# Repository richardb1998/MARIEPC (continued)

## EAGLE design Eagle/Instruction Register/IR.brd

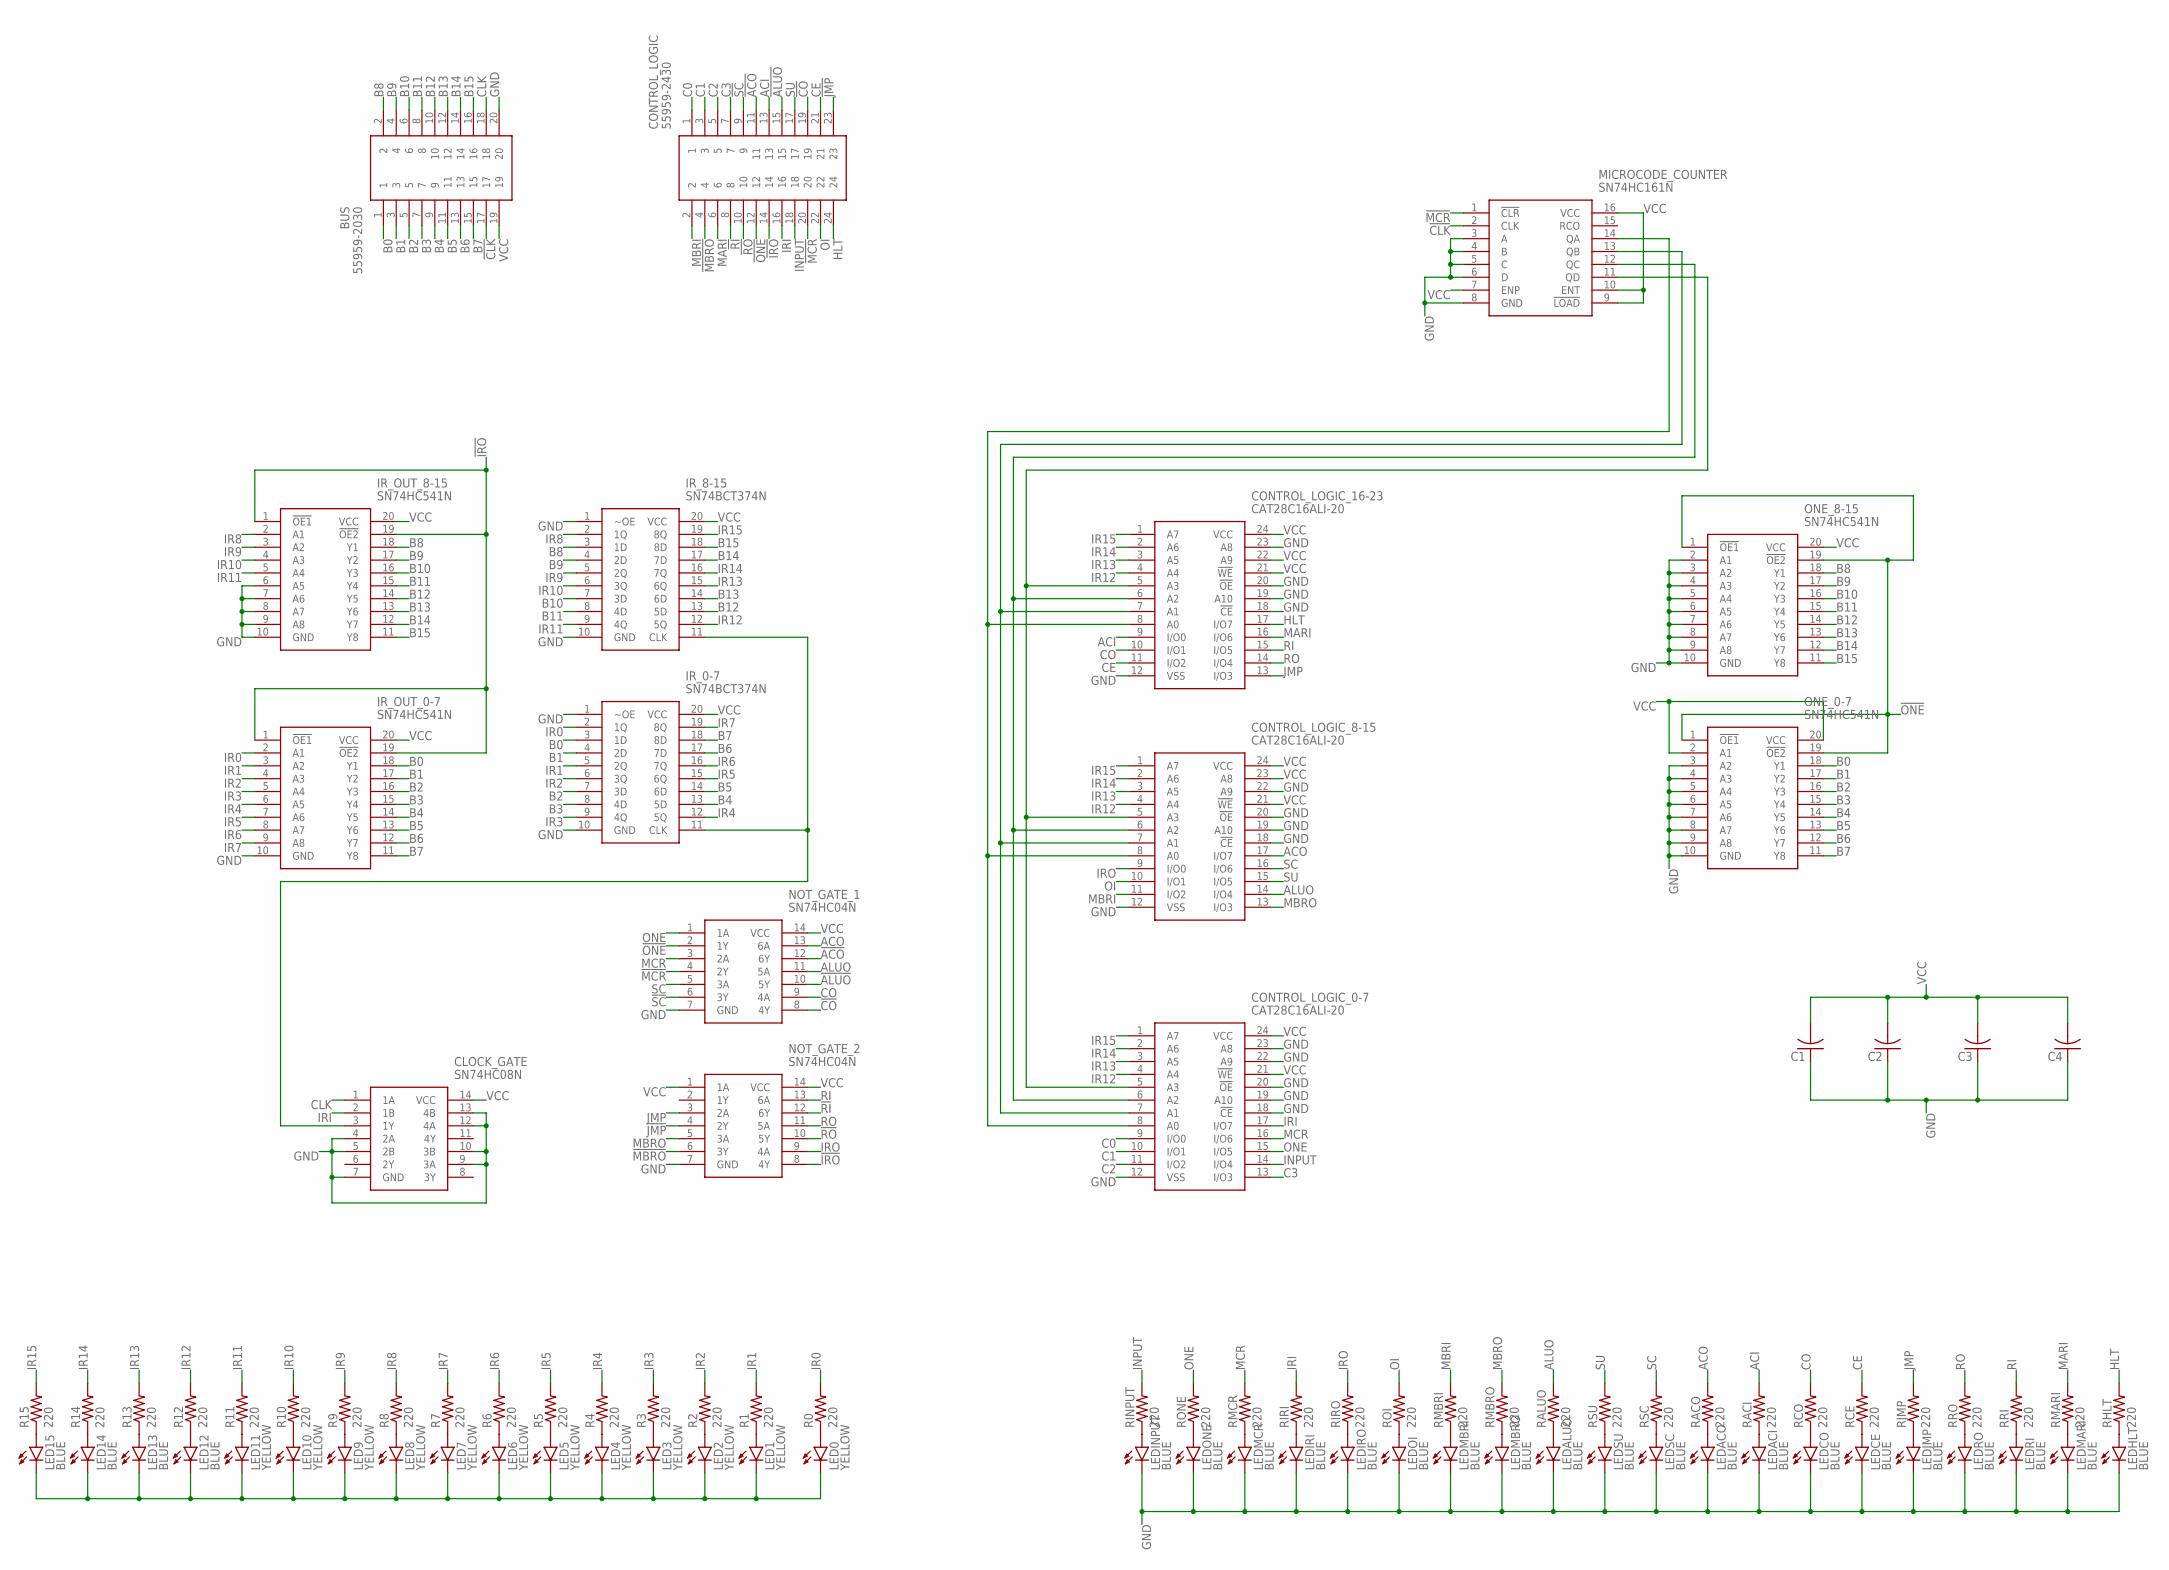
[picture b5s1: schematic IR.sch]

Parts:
BUS: 55959-2030; 55959-2030_1
C1, C2, C3, C4: C-US025-024X044; C025-024X044
CLOCK_GATE: SN74HC08N; DIP794W53P254L1930H508Q14N
CONTROL_LOGIC: 55959-2430; 559592430
CONTROL_LOGIC_0-7, CONTROL_LOGIC_8-15, CONTROL_LOGIC_16-23: CAT28C16ALI-20; DIP1651W55P254L3188H635Q24N
IR_0-7, IR_8-15: SN74BCT374N; DIP254P762X508-20
IR_OUT_0-7, IR_OUT_8-15: SN74HC541N; DIP794W53P254L2540H508Q20N
LED0, LED1, LED2, LED3, LED4, LED5, LED6, LED7, LED8, LED9, LED10, LED11: YELLOW; LED3MM
LED12, LED13, LED14, LED15: BLUE; LED3MM
LEDACI: BLUE; LED3MM
LEDACO: BLUE; LED3MM
LEDALUO: BLUE; LED3MM
LEDCE: BLUE; LED3MM
LEDCO: BLUE; LED3MM
LEDHLT: BLUE; LED3MM
LEDINPUT: BLUE; LED3MM
LEDIRI: BLUE; LED3MM
LEDIRO: BLUE; LED3MM
LEDJMP: BLUE; LED3MM
LEDMARI: BLUE; LED3MM
LEDMBRI: BLUE; LED3MM
LEDMBRO: BLUE; LED3MM
LEDMCR: BLUE; LED3MM
LEDOI: BLUE; LED3MM
LEDONE: BLUE; LED3MM
LEDRI: BLUE; LED3MM
LEDRO: BLUE; LED3MM
LEDSC: BLUE; LED3MM
LEDSU: BLUE; LED3MM
MICROCODE_COUNTER: SN74HC161N; DIP794W53P254L1930H508Q16N
NOT_GATE_1, NOT_GATE_2: SN74HC04N; DIP794W53P254L1930H508Q14N
ONE_0-7, ONE_8-15: SN74HC541N; DIP794W53P254L2540H508Q20N
R0, R1, R2, R3, R4, R5, R6, R7, R8, R9, R10, R11, R12, R13, R14, R15: 220; 0204/7
RACI: 220; 0204/7
RACO: 220; 0204/7
RALUO: 220; 0204/7
RCE: 220; 0204/7
RCO: 220; 0204/7
RHLT: 220; 0204/7
RINPUT: 220; 0204/7
RIRI: 220; 0204/7
RIRO: 220; 0204/7
RJMP: 220; 0204/7
RMARI: 220; 0204/7
RMBRI: 220; 0204/7
RMBRO: 220; 0204/7
RMCR: 220; 0204/7
ROI: 220; 0204/7
RONE: 220; 0204/7
RRI: 220; 0204/7
RRO: 220; 0204/7
RSC: 220; 0204/7
RSU: 220; 0204/7

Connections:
!ACO: CONTROL_LOGIC.11, NOT_GATE_1.12 (6Y)
!ALUO: CONTROL_LOGIC.15, NOT_GATE_1.10 (5Y)
!CLK: BUS.17, MICROCODE_COUNTER.2 (CLK)
!CO: CONTROL_LOGIC.19, NOT_GATE_1.8 (4Y)
!IRO: CONTROL_LOGIC.14, IR_OUT_0-7.1 (!OE1), IR_OUT_0-7.19 (!OE2), IR_OUT_8-15.1 (!OE1), IR_OUT_8-15.19 (!OE2), NOT_GATE_2.8 (4Y)
!JMP: CONTROL_LOGIC.23, NOT_GATE_2.4 (2Y)
!MBRO: CONTROL_LOGIC.4, NOT_GATE_2.6 (3Y)
!MCR: CONTROL_LOGIC.20, MICROCODE_COUNTER.1 (!CLR), NOT_GATE_1.4 (2Y)
!ONE: CONTROL_LOGIC.12, NOT_GATE_1.2 (1Y), ONE_0-7.1 (!OE1), ONE_0-7.19 (!OE2), ONE_8-15.1 (!OE1), ONE_8-15.19 (!OE2)
!RI: CONTROL_LOGIC.8, NOT_GATE_2.12 (6Y)
!RO: CONTROL_LOGIC.10, NOT_GATE_2.10 (5Y)
!SC: CONTROL_LOGIC.9, NOT_GATE_1.6 (3Y)
ACI: CONTROL_LOGIC.13, CONTROL_LOGIC_16-23.9 (I/O0), RACI.2
ACO: CONTROL_LOGIC_8-15.17 (I/O7), NOT_GATE_1.13 (6A), RACO.2
ALUO: CONTROL_LOGIC_8-15.14 (I/O4), NOT_GATE_1.11 (5A), RALUO.2
B0: BUS.1, IR_0-7.3 (1D), IR_OUT_0-7.18 (Y1), ONE_0-7.18 (Y1)
B1: BUS.3, IR_0-7.4 (2D), IR_OUT_0-7.17 (Y2), ONE_0-7.17 (Y2)
B2: BUS.5, IR_0-7.7 (3D), IR_OUT_0-7.16 (Y3), ONE_0-7.16 (Y3)
B3: BUS.7, IR_0-7.8 (4D), IR_OUT_0-7.15 (Y4), ONE_0-7.15 (Y4)
B4: BUS.9, IR_0-7.13 (5D), IR_OUT_0-7.14 (Y5), ONE_0-7.14 (Y5)
B5: BUS.11, IR_0-7.14 (6D), IR_OUT_0-7.13 (Y6), ONE_0-7.13 (Y6)
B6: BUS.13, IR_0-7.17 (7D), IR_OUT_0-7.12 (Y7), ONE_0-7.12 (Y7)
B7: BUS.15, IR_0-7.18 (8D), IR_OUT_0-7.11 (Y8), ONE_0-7.11 (Y8)
B8: BUS.2, IR_8-15.3 (1D), IR_OUT_8-15.18 (Y1), ONE_8-15.18 (Y1)
B9: BUS.4, IR_8-15.4 (2D), IR_OUT_8-15.17 (Y2), ONE_8-15.17 (Y2)
B10: BUS.6, IR_8-15.7 (3D), IR_OUT_8-15.16 (Y3), ONE_8-15.16 (Y3)
B11: BUS.8, IR_8-15.8 (4D), IR_OUT_8-15.15 (Y4), ONE_8-15.15 (Y4)
B12: BUS.10, IR_8-15.13 (5D), IR_OUT_8-15.14 (Y5), ONE_8-15.14 (Y5)
B13: BUS.12, IR_8-15.14 (6D), IR_OUT_8-15.13 (Y6), ONE_8-15.13 (Y6)
B14: BUS.14, IR_8-15.17 (7D), IR_OUT_8-15.12 (Y7), ONE_8-15.12 (Y7)
B15: BUS.16, IR_8-15.18 (8D), IR_OUT_8-15.11 (Y8), ONE_8-15.11 (Y8)
C0: CONTROL_LOGIC.1, CONTROL_LOGIC_0-7.9 (I/O0)
C1: CONTROL_LOGIC.3, CONTROL_LOGIC_0-7.10 (I/O1)
C2: CONTROL_LOGIC.5, CONTROL_LOGIC_0-7.11 (I/O2)
C3: CONTROL_LOGIC.7, CONTROL_LOGIC_0-7.13 (I/O3)
CE: CONTROL_LOGIC.21, CONTROL_LOGIC_16-23.11 (I/O2), RCE.2
CLK: BUS.18, CLOCK_GATE.1 (1A)
CO: CONTROL_LOGIC_16-23.10 (I/O1), NOT_GATE_1.9 (4A), RCO.2
GND: BUS.20, C1.1, C2.1, C3.1, C4.1, CLOCK_GATE.4 (2A), CLOCK_GATE.5 (2B), CLOCK_GATE.7 (GND), CLOCK_GATE.9 (3A), CLOCK_GATE.10 (3B), CLOCK_GATE.12 (4A), CLOCK_GATE.13 (4B), CONTROL_LOGIC_0-7.12 (VSS), CONTROL_LOGIC_0-7.18 (!CE), CONTROL_LOGIC_0-7.19 (A10), CONTROL_LOGIC_0-7.20 (!OE), CONTROL_LOGIC_0-7.22 (A9), CONTROL_LOGIC_0-7.23 (A8), CONTROL_LOGIC_8-15.12 (VSS), CONTROL_LOGIC_8-15.18 (!CE), CONTROL_LOGIC_8-15.19 (A10), CONTROL_LOGIC_8-15.20 (!OE), CONTROL_LOGIC_8-15.22 (A9), CONTROL_LOGIC_16-23.12 (VSS), CONTROL_LOGIC_16-23.18 (!CE), CONTROL_LOGIC_16-23.19 (A10), CONTROL_LOGIC_16-23.20 (!OE), CONTROL_LOGIC_16-23.23 (A8), IR_0-7.1 (~OE), IR_0-7.10 (GND), IR_8-15.1 (~OE), IR_8-15.10 (GND), IR_OUT_0-7.10 (GND), IR_OUT_8-15.6 (A5), IR_OUT_8-15.7 (A6), IR_OUT_8-15.8 (A7), IR_OUT_8-15.9 (A8), IR_OUT_8-15.10 (GND), LEDACI.K (C), LEDACO.K (C), LEDALUO.K (C), LEDCE.K (C), LEDCO.K (C), LEDHLT.K (C), LEDINPUT.K (C), LEDIRI.K (C), LEDIRO.K (C), LEDJMP.K (C), LEDMARI.K (C), LEDMBRI.K (C), LEDMBRO.K (C), LEDMCR.K (C), LEDOI.K (C), LEDONE.K (C), LEDRI.K (C), LEDRO.K (C), LEDSC.K (C), LEDSU.K (C), MICROCODE_COUNTER.3 (A), MICROCODE_COUNTER.4 (B), MICROCODE_COUNTER.5 (C), MICROCODE_COUNTER.6 (D), MICROCODE_COUNTER.8 (GND), NOT_GATE_1.7 (GND), NOT_GATE_2.7 (GND), ONE_0-7.3 (A2), ONE_0-7.4 (A3), ONE_0-7.5 (A4), ONE_0-7.6 (A5), ONE_0-7.7 (A6), ONE_0-7.8 (A7), ONE_0-7.9 (A8), ONE_0-7.10 (GND), ONE_8-15.2 (A1), ONE_8-15.3 (A2), ONE_8-15.4 (A3), ONE_8-15.5 (A4), ONE_8-15.6 (A5), ONE_8-15.7 (A6), ONE_8-15.8 (A7), ONE_8-15.9 (A8), ONE_8-15.10 (GND)
HLT: CONTROL_LOGIC.24, CONTROL_LOGIC_16-23.17 (I/O7), RHLT.2
INPUT: CONTROL_LOGIC.18, CONTROL_LOGIC_0-7.14 (I/O4), RINPUT.2
IR0: IR_0-7.2 (1Q), IR_OUT_0-7.2 (A1), R0.2
IR1: IR_0-7.5 (2Q), IR_OUT_0-7.3 (A2), R1.2
IR2: IR_0-7.6 (3Q), IR_OUT_0-7.4 (A3), R2.2
IR3: IR_0-7.9 (4Q), IR_OUT_0-7.5 (A4), R3.2
IR4: IR_0-7.12 (5Q), IR_OUT_0-7.6 (A5), R4.2
IR5: IR_0-7.15 (6Q), IR_OUT_0-7.7 (A6), R5.2
IR6: IR_0-7.16 (7Q), IR_OUT_0-7.8 (A7), R6.2
IR7: IR_0-7.19 (8Q), IR_OUT_0-7.9 (A8), R7.2
IR8: IR_8-15.2 (1Q), IR_OUT_8-15.2 (A1), R8.2
IR9: IR_8-15.5 (2Q), IR_OUT_8-15.3 (A2), R9.2
IR10: IR_8-15.6 (3Q), IR_OUT_8-15.4 (A3), R10.2
IR11: IR_8-15.9 (4Q), IR_OUT_8-15.5 (A4), R11.2
IR12: CONTROL_LOGIC_0-7.4 (A4), CONTROL_LOGIC_8-15.4 (A4), CONTROL_LOGIC_16-23.4 (A4), IR_8-15.12 (5Q), R12.2
IR13: CONTROL_LOGIC_0-7.3 (A5), CONTROL_LOGIC_8-15.3 (A5), CONTROL_LOGIC_16-23.3 (A5), IR_8-15.15 (6Q), R13.2
IR14: CONTROL_LOGIC_0-7.2 (A6), CONTROL_LOGIC_8-15.2 (A6), CONTROL_LOGIC_16-23.2 (A6), IR_8-15.16 (7Q), R14.2
IR15: CONTROL_LOGIC_0-7.1 (A7), CONTROL_LOGIC_8-15.1 (A7), CONTROL_LOGIC_16-23.1 (A7), IR_8-15.19 (8Q), R15.2
IRI: CLOCK_GATE.2 (1B), CONTROL_LOGIC.16, CONTROL_LOGIC_0-7.17 (I/O7), RIRI.2
IRO: CONTROL_LOGIC_8-15.9 (I/O0), NOT_GATE_2.9 (4A), RIRO.2
JMP: CONTROL_LOGIC_16-23.13 (I/O3), NOT_GATE_2.3 (2A), RJMP.2
MARI: CONTROL_LOGIC.6, CONTROL_LOGIC_16-23.16 (I/O6), RMARI.2
MBRI: CONTROL_LOGIC.2, CONTROL_LOGIC_8-15.11 (I/O2), RMBRI.2
MBRO: CONTROL_LOGIC_8-15.13 (I/O3), NOT_GATE_2.5 (3A), RMBRO.2
MCR: CONTROL_LOGIC_0-7.16 (I/O6), NOT_GATE_1.3 (2A), RMCR.2
unnamed: CONTROL_LOGIC_0-7.8 (A0), CONTROL_LOGIC_8-15.8 (A0), CONTROL_LOGIC_16-23.8 (A0), MICROCODE_COUNTER.14 (QA)
unnamed: CONTROL_LOGIC_0-7.7 (A1), CONTROL_LOGIC_8-15.7 (A1), CONTROL_LOGIC_16-23.7 (A1), MICROCODE_COUNTER.13 (QB)
unnamed: CONTROL_LOGIC_0-7.6 (A2), CONTROL_LOGIC_8-15.6 (A2), CONTROL_LOGIC_16-23.6 (A2), MICROCODE_COUNTER.12 (QC)
unnamed: CONTROL_LOGIC_0-7.5 (A3), CONTROL_LOGIC_8-15.5 (A3), CONTROL_LOGIC_16-23.5 (A3), MICROCODE_COUNTER.11 (QD)
unnamed: LEDINPUT.A, RINPUT.1
unnamed: LEDONE.A, RONE.1
unnamed: LEDMCR.A, RMCR.1
unnamed: LEDIRI.A, RIRI.1
unnamed: LEDIRO.A, RIRO.1
unnamed: LEDOI.A, ROI.1
unnamed: LEDMBRI.A, RMBRI.1
unnamed: LEDALUO.A, RALUO.1
unnamed: LEDSU.A, RSU.1
unnamed: LEDSC.A, RSC.1
unnamed: LEDCO.A, RCO.1
unnamed: LEDJMP.A, RJMP.1
unnamed: LEDRO.A, RRO.1
unnamed: LEDRI.A, RRI.1
unnamed: LEDMARI.A, RMARI.1
unnamed: LEDMBRO.A, RMBRO.1
unnamed: LEDACO.A, RACO.1
unnamed: LEDACI.A, RACI.1
unnamed: LEDCE.A, RCE.1
unnamed: LEDHLT.A, RHLT.1
unnamed: LED1.A, R1.1
unnamed: LED2.A, R2.1
unnamed: LED3.A, R3.1
unnamed: LED4.A, R4.1
unnamed: LED5.A, R5.1
unnamed: LED6.A, R6.1
unnamed: LED7.A, R7.1
unnamed: LED8.A, R8.1
unnamed: CLOCK_GATE.3 (1Y), IR_0-7.11 (CLK), IR_8-15.11 (CLK)
unnamed: LED9.A, R9.1
unnamed: LED10.A, R10.1
unnamed: LED11.A, R11.1
unnamed: LED12.A, R12.1
unnamed: LED13.A, R13.1
unnamed: LED14.A, R14.1
unnamed: LED15.A, R15.1
unnamed: LED0.A, R0.1
unnamed: LED0.K (C), LED1.K (C), LED2.K (C), LED3.K (C), LED4.K (C), LED5.K (C), LED6.K (C), LED7.K (C), LED8.K (C), LED9.K (C), LED10.K (C), LED11.K (C), LED12.K (C), LED13.K (C), LED14.K (C), LED15.K (C)
OI: CONTROL_LOGIC.22, CONTROL_LOGIC_8-15.10 (I/O1), ROI.2
ONE: CONTROL_LOGIC_0-7.15 (I/O5), NOT_GATE_1.1 (1A), RONE.2
RI: CONTROL_LOGIC_16-23.15 (I/O5), NOT_GATE_2.13 (6A), RRI.2
RO: CONTROL_LOGIC_16-23.14 (I/O4), NOT_GATE_2.11 (5A), RRO.2
SC: CONTROL_LOGIC_8-15.16 (I/O6), NOT_GATE_1.5 (3A), RSC.2
SU: CONTROL_LOGIC.17, CONTROL_LOGIC_8-15.15 (I/O5), RSU.2
VCC: BUS.19, C1.2, C2.2, C3.2, C4.2, CLOCK_GATE.14 (VCC), CONTROL_LOGIC_0-7.21 (!WE), CONTROL_LOGIC_0-7.24 (VCC), CONTROL_LOGIC_8-15.21 (!WE), CONTROL_LOGIC_8-15.23 (A8), CONTROL_LOGIC_8-15.24 (VCC), CONTROL_LOGIC_16-23.21 (!WE), CONTROL_LOGIC_16-23.22 (A9), CONTROL_LOGIC_16-23.24 (VCC), IR_0-7.20 (VCC), IR_8-15.20 (VCC), IR_OUT_0-7.20 (VCC), IR_OUT_8-15.20 (VCC), MICROCODE_COUNTER.7 (ENP), MICROCODE_COUNTER.9 (!LOAD), MICROCODE_COUNTER.10 (ENT), MICROCODE_COUNTER.16 (VCC), NOT_GATE_1.14 (VCC), NOT_GATE_2.1 (1A), NOT_GATE_2.14 (VCC), ONE_0-7.2 (A1), ONE_0-7.20 (VCC), ONE_8-15.20 (VCC)

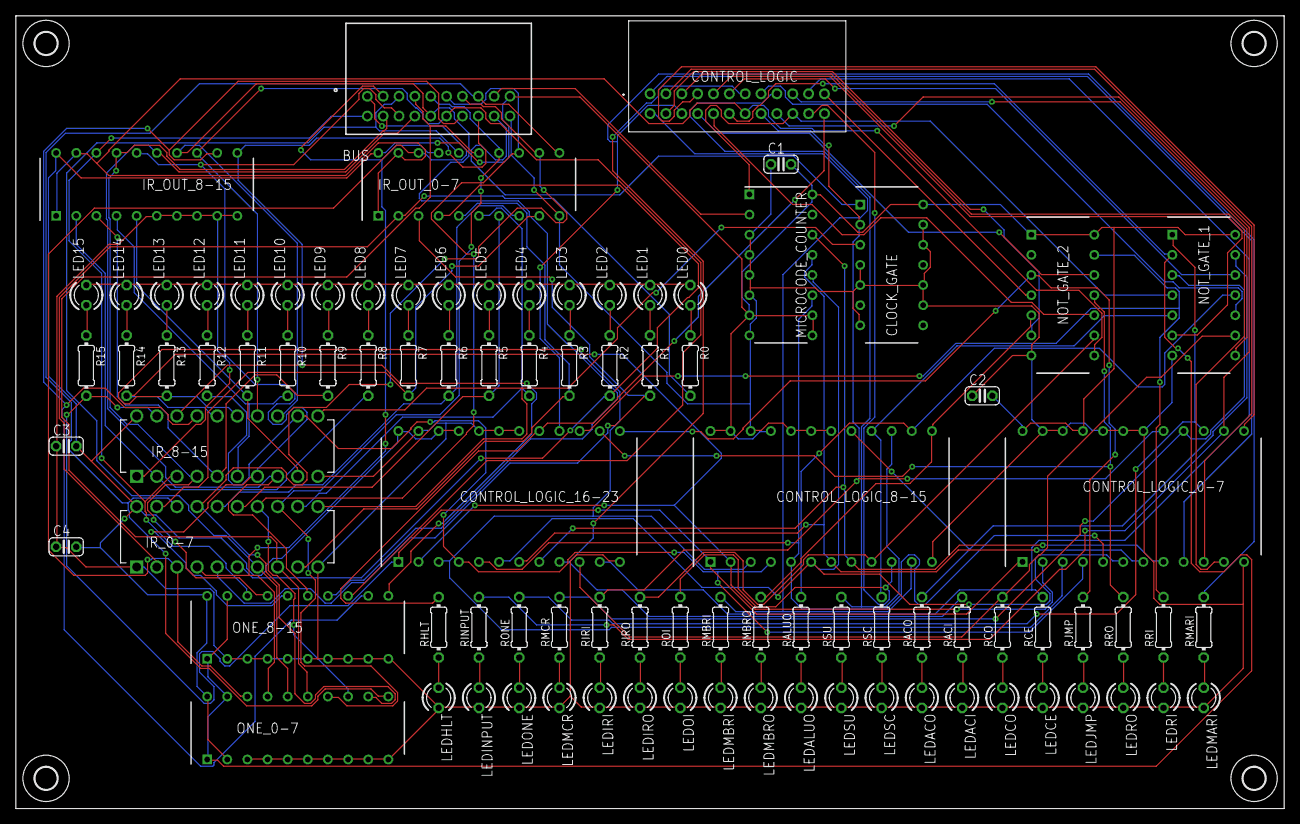
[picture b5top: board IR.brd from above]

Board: 2 copper layers, 160.0 x 100.0 mm, 95 parts (0 on the bottom side), 113 nets.

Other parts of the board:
U$1, U$2, U$3, U$4: 2,8

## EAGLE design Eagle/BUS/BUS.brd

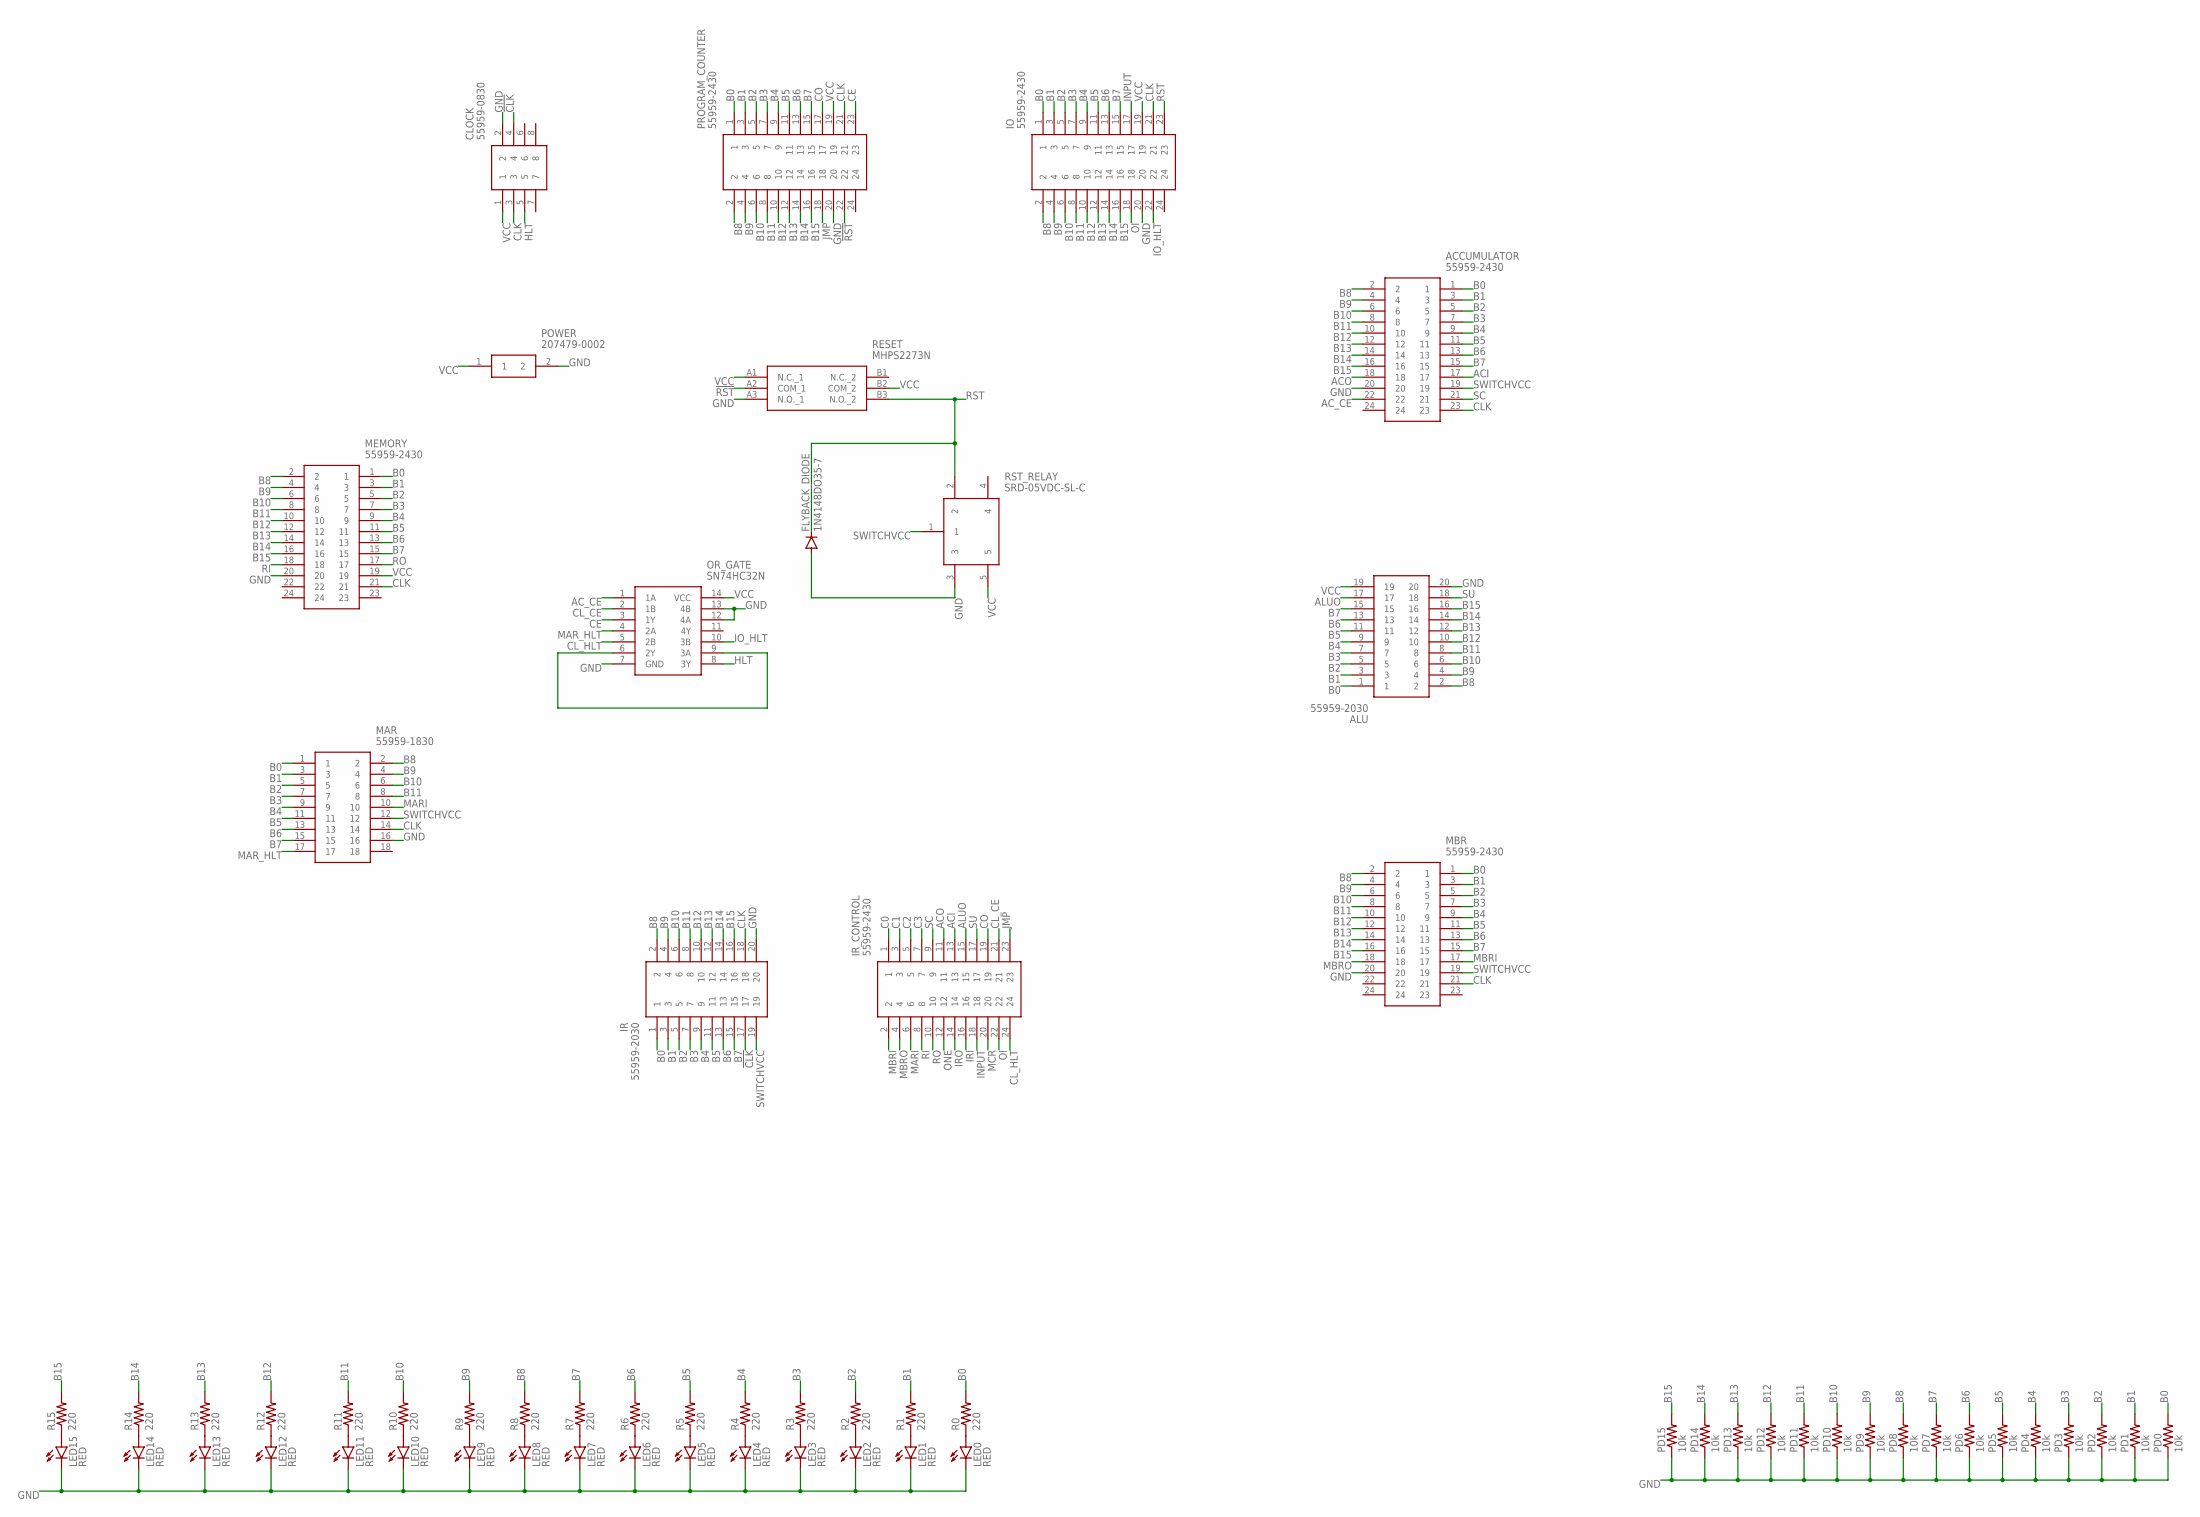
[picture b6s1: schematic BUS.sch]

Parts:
ACCUMULATOR: 55959-2430; 559592430
ALU: 55959-2030; 55959-2030_1
CLOCK: 55959-0830; SHDR8W65P250X200_2X4_1140X1400
FLYBACK_DIODE: 1N4148DO35-7; DO35-7
IO: 55959-2430; 559592430
IR: 55959-2030; 55959-2030_1
IR_CONTROL: 55959-2430; 559592430
LED0, LED1, LED2, LED3, LED4, LED5, LED6, LED7, LED8, LED9, LED10, LED11, LED12, LED13, LED14, LED15: RED; LED3MM
MAR: 55959-1830; SHDR18W65P250X200_2X9_2140X140
MBR: 55959-2430; 559592430
MEMORY: 55959-2430; 559592430
OR_GATE: SN74HC32N; DIP794W53P254L1930H508Q14N
PD0, PD1, PD2, PD3, PD4, PD5, PD6, PD7, PD8, PD9, PD10, PD11, PD12, PD13, PD14, PD15: 10k; 0204/7
POWER: 207479-0002; 2074790002
PROGRAM_COUNTER: 55959-2430; 559592430
R0, R1, R2, R3, R4, R5, R6, R7, R8, R9, R10, R11, R12, R13, R14, R15: 220; 0204/7
RESET: MHPS2273N
RST_RELAY: SRD-05VDC-SL-C; SRD

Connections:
!CLK: CLOCK.4, IR.17
!RST: PROGRAM_COUNTER.22, RESET.A2 (COM_1)
ACI: ACCUMULATOR.17, IR_CONTROL.13
ACO: ACCUMULATOR.18, IR_CONTROL.11
AC_CE: ACCUMULATOR.22, OR_GATE.1 (1A)
ALUO: ALU.17, IR_CONTROL.15
B0: ACCUMULATOR.1, ALU.1, IO.1, IR.1, MAR.1, MBR.1, MEMORY.1, PD0.2, PROGRAM_COUNTER.1, R0.2
B1: ACCUMULATOR.3, ALU.3, IO.3, IR.3, MAR.3, MBR.3, MEMORY.3, PD1.2, PROGRAM_COUNTER.3, R1.2
B2: ACCUMULATOR.5, ALU.5, IO.5, IR.5, MAR.5, MBR.5, MEMORY.5, PD2.2, PROGRAM_COUNTER.5, R2.2
B3: ACCUMULATOR.7, ALU.7, IO.7, IR.7, MAR.7, MBR.7, MEMORY.7, PD3.2, PROGRAM_COUNTER.7, R3.2
B4: ACCUMULATOR.9, ALU.9, IO.9, IR.9, MAR.9, MBR.9, MEMORY.9, PD4.2, PROGRAM_COUNTER.9, R4.2
B5: ACCUMULATOR.11, ALU.11, IO.11, IR.11, MAR.11, MBR.11, MEMORY.11, PD5.2, PROGRAM_COUNTER.11, R5.2
B6: ACCUMULATOR.13, ALU.13, IO.13, IR.13, MAR.13, MBR.13, MEMORY.13, PD6.2, PROGRAM_COUNTER.13, R6.2
B7: ACCUMULATOR.15, ALU.15, IO.15, IR.15, MAR.15, MBR.15, MEMORY.15, PD7.2, PROGRAM_COUNTER.15, R7.2
B8: ACCUMULATOR.2, ALU.2, IO.2, IR.2, MAR.2, MBR.2, MEMORY.2, PD8.2, PROGRAM_COUNTER.2, R8.2
B9: ACCUMULATOR.4, ALU.4, IO.4, IR.4, MAR.4, MBR.4, MEMORY.4, PD9.2, PROGRAM_COUNTER.4, R9.2
B10: ACCUMULATOR.6, ALU.6, IO.6, IR.6, MAR.6, MBR.6, MEMORY.6, PD10.2, PROGRAM_COUNTER.6, R10.2
B11: ACCUMULATOR.8, ALU.8, IO.8, IR.8, MAR.8, MBR.8, MEMORY.8, PD11.2, PROGRAM_COUNTER.8, R11.2
B12: ACCUMULATOR.10, ALU.10, IO.10, IR.10, MBR.10, MEMORY.10, PD12.2, PROGRAM_COUNTER.10, R12.2
B13: ACCUMULATOR.12, ALU.12, IO.12, IR.12, MBR.12, MEMORY.12, PD13.2, PROGRAM_COUNTER.12, R13.2
B14: ACCUMULATOR.14, ALU.14, IO.14, IR.14, MBR.14, MEMORY.14, PD14.2, PROGRAM_COUNTER.14, R14.2
B15: ACCUMULATOR.16, ALU.16, IO.16, IR.16, MBR.16, MEMORY.16, PD15.2, PROGRAM_COUNTER.16, R15.2
C0: IR_CONTROL.1
C1: IR_CONTROL.3
C2: IR_CONTROL.5
C3: IR_CONTROL.7
CE: OR_GATE.3 (1Y), PROGRAM_COUNTER.23
CLK: ACCUMULATOR.23, CLOCK.3, IO.21, IR.18, MAR.14, MBR.21, MEMORY.21, PROGRAM_COUNTER.21
CL_CE: IR_CONTROL.21, OR_GATE.2 (1B)
CL_HLT: IR_CONTROL.24, OR_GATE.5 (2B)
CO: IR_CONTROL.19, PROGRAM_COUNTER.17
GND: ACCUMULATOR.20, ALU.20, CLOCK.2, FLYBACK_DIODE.A, IO.20, IR.20, LED0.K (C), LED1.K (C), LED2.K (C), LED3.K (C), LED4.K (C), LED5.K (C), LED6.K (C), LED7.K (C), LED8.K (C), LED9.K (C), LED10.K (C), LED11.K (C), LED12.K (C), LED13.K (C), LED14.K (C), LED15.K (C), MAR.16, MBR.20, MEMORY.20, OR_GATE.7 (GND), OR_GATE.12 (4A), OR_GATE.13 (4B), PD0.1, PD1.1, PD2.1, PD3.1, PD4.1, PD5.1, PD6.1, PD7.1, PD8.1, PD9.1, PD10.1, PD11.1, PD12.1, PD13.1, PD14.1, PD15.1, POWER.2, PROGRAM_COUNTER.20, RESET.A3 (N.O._1), RST_RELAY.3
HLT: CLOCK.5, OR_GATE.8 (3Y)
INPUT: IO.17, IR_CONTROL.18
IO_HLT: IO.22, OR_GATE.10 (3B)
IRI: IR_CONTROL.16
IRO: IR_CONTROL.14
JMP: IR_CONTROL.23, PROGRAM_COUNTER.18
MARI: IR_CONTROL.6, MAR.10
MAR_HLT: MAR.17, OR_GATE.4 (2A)
MBRI: IR_CONTROL.2, MBR.17
MBRO: IR_CONTROL.4, MBR.18
MCR: IR_CONTROL.20
unnamed: LED1.A, R1.1
unnamed: LED2.A, R2.1
unnamed: LED3.A, R3.1
unnamed: LED4.A, R4.1
unnamed: LED5.A, R5.1
unnamed: LED6.A, R6.1
unnamed: LED7.A, R7.1
unnamed: LED8.A, R8.1
unnamed: OR_GATE.6 (2Y), OR_GATE.9 (3A)
unnamed: LED9.A, R9.1
unnamed: LED10.A, R10.1
unnamed: LED11.A, R11.1
unnamed: LED12.A, R12.1
unnamed: LED13.A, R13.1
unnamed: LED14.A, R14.1
unnamed: LED15.A, R15.1
unnamed: LED0.A, R0.1
OI: IO.18, IR_CONTROL.22
ONE: IR_CONTROL.12
RI: IR_CONTROL.8, MEMORY.18
RO: IR_CONTROL.10, MEMORY.17
RST: FLYBACK_DIODE.C, IO.23, RESET.B3 (N.O._2), RST_RELAY.2
SC: ACCUMULATOR.21, IR_CONTROL.9
SU: ALU.18, IR_CONTROL.17
SWITCHVCC: ACCUMULATOR.19, IR.19, MAR.12, MBR.19, RST_RELAY.1
VCC: ALU.19, CLOCK.1, IO.19, MEMORY.19, OR_GATE.14 (VCC), POWER.1, PROGRAM_COUNTER.19, RESET.A1 (N.C._1), RESET.B2 (COM_2), RST_RELAY.5

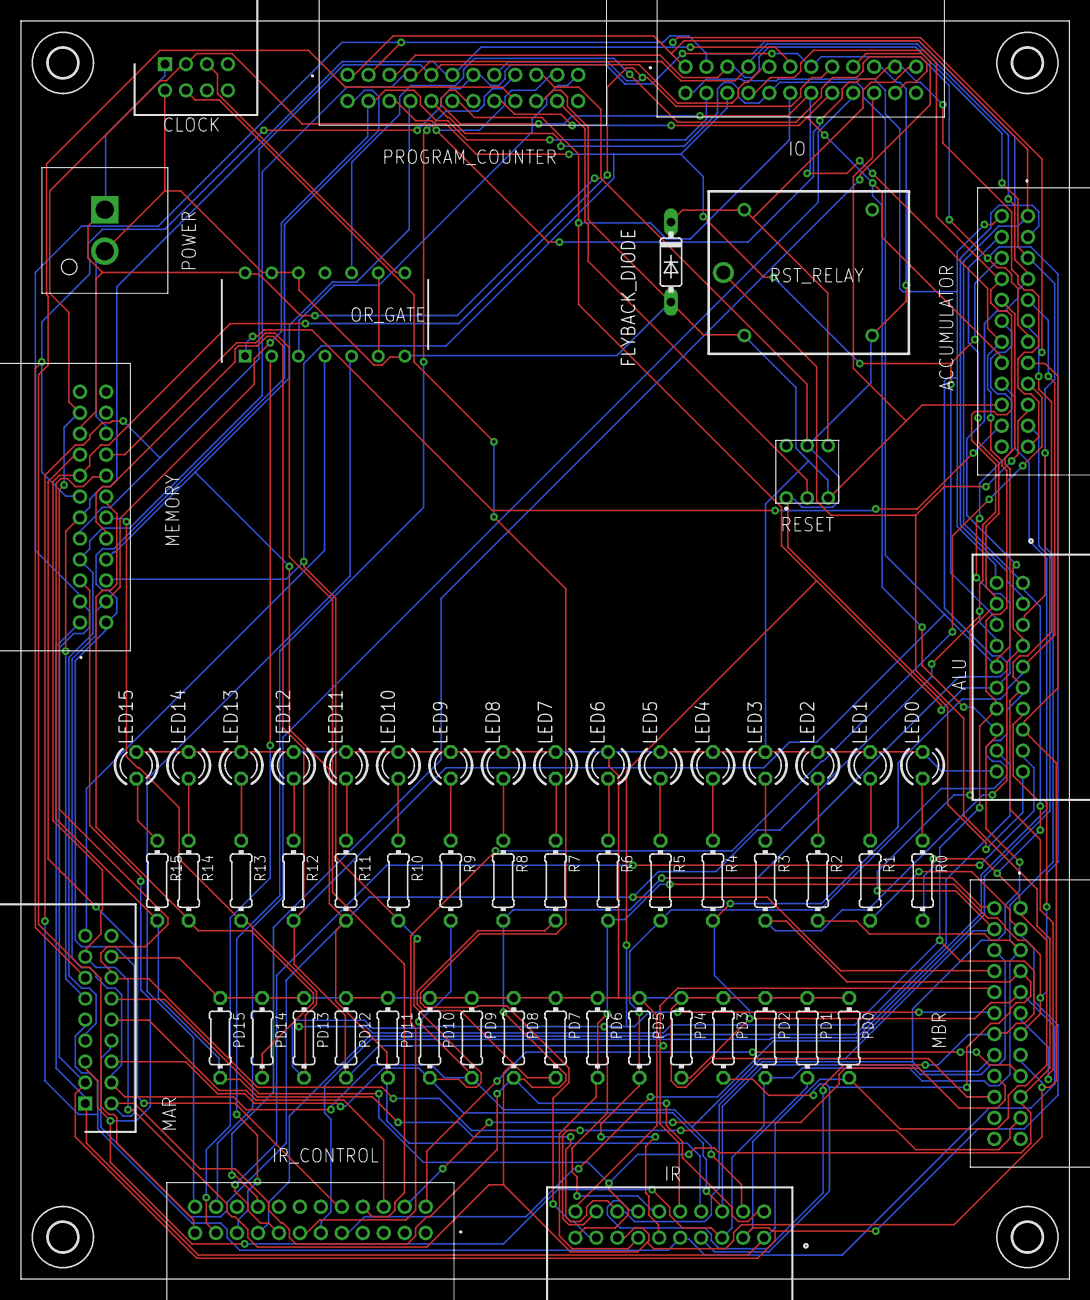
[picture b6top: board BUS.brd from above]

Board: 2 copper layers, 100.0 x 120.0 mm, 67 parts (0 on the bottom side), 61 nets.

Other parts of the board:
U$1, U$2, U$3, U$4: 2,8
